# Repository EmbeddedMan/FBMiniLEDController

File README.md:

# FBMiniLEDController
DotStar/NeoPixel controller board for Fubarino Mini chipKIT board

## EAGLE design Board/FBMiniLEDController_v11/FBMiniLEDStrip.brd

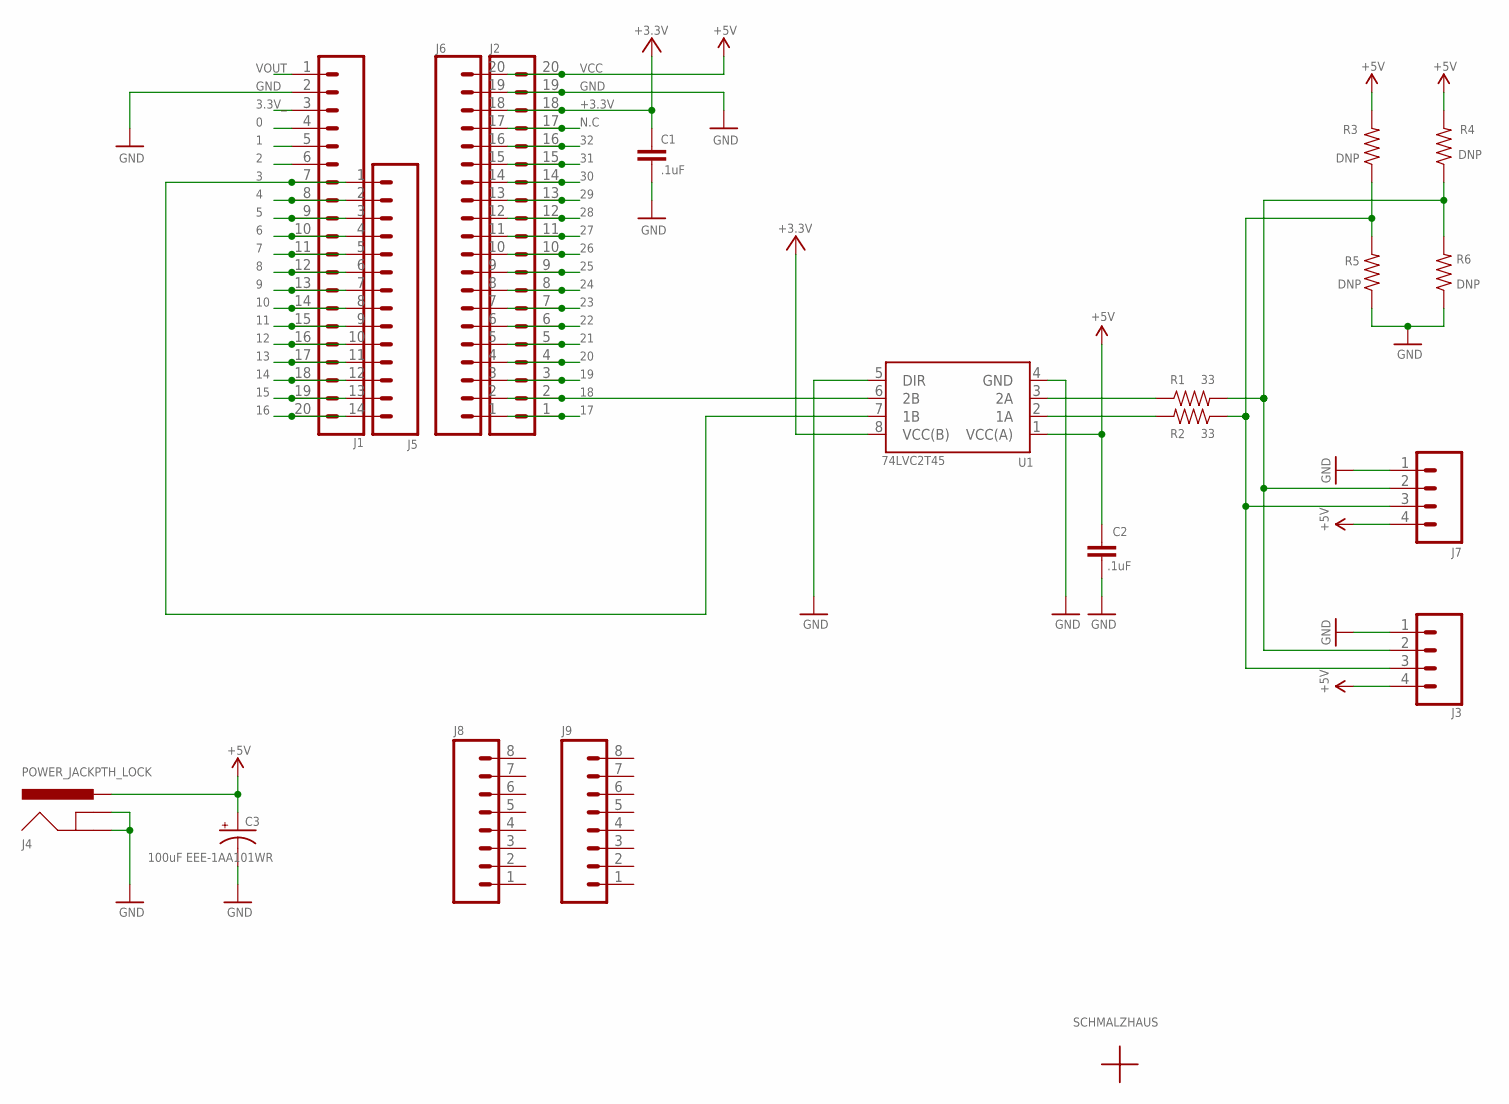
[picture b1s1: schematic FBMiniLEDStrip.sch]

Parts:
C1, C2: .1uF; 0603-CAP
C3: 100uF EEE-1AA101WR; PANASONIC_C
J1, J2, J6: CONN_20; 1X20
J3: CONN_04SCREW; SCREWTERMINAL-3.5MM-4@1
J4: POWER_JACKPTH_LOCK; POWER_JACK_PTH_LOCK
J5: M14; 1X14
J7: M04PTH; 1X04
J8, J9: M08; 1X08_ROUND
R1, R2: 33; 0603-RES
R3, R4, R5, R6: DNP; 0603-RES
U1: 74LVC2T45; VSSOP8
U$1: SCHMALZHAUSSCHMALZHAUS_SMALL; SCHMALZHAUS_SMALL

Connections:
0: J1.4
1: J1.5
2: J1.6
3: J1.7, J5.1, U1.7 (1B)
3.3V_: J1.3
4: J1.8, J5.2
5: J1.9, J5.3
6: J1.10, J5.4
7: J1.11, J5.5
8: J1.12, J5.6
9: J1.13, J5.7
10: J1.14, J5.8
11: J1.15, J5.9
12: J1.16, J5.10
13: J1.17, J5.11
14: J1.18, J5.12
15: J1.19, J5.13
16: J1.20, J5.14
17: J2.1, J6.1
18: J2.2, J6.2, U1.6 (2B)
19: J2.3, J6.3
20: J2.4, J6.4
21: J2.5, J6.5
22: J2.6, J6.6
23: J2.7, J6.7
24: J2.8, J6.8
25: J2.9, J6.9
26: J2.10, J6.10
27: J2.11, J6.11
28: J2.12, J6.12
29: J2.13, J6.13
30: J2.14, J6.14
31: J2.15, J6.15
32: J2.16, J6.16
+3.3V: C1.1, J2.18, J6.18
+3V3: U1.8 (VCC(B))
GND: C1.2, C2.1, C3.-, J1.2, J2.19, J3.1, J4.GND, J4.GNDBREAK, J6.19, J7.1, R5.1, R6.1, U1.4 (GND), U1.5 (DIR)
unnamed: J3.2, J7.2, R1.2, R4.1, R6.2
unnamed: R2.2, U1.2 (1A)
unnamed: J3.3, J7.3, R2.1, R3.1, R5.2
unnamed: R1.1, U1.3 (2A)
N.C: J2.17, J6.17
VCC: C2.2, C3.+, J2.20, J3.4, J4.PWR, J6.20, J7.4, R3.2, R4.2, U1.1 (VCC(A))
VOUT: J1.1

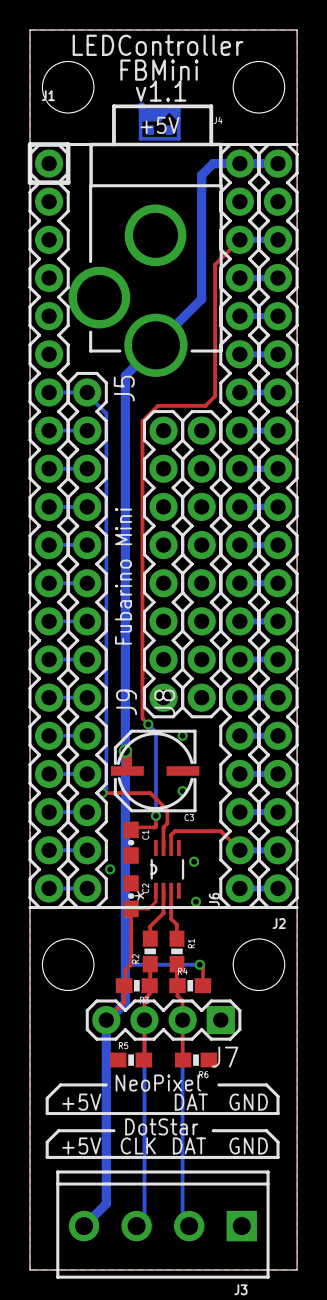
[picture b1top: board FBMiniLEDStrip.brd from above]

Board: 2 copper layers, 17.8 x 82.5 mm, 20 parts (1 on the bottom side), 38 nets.

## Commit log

2017-06-17 Adding initial files.
2017-07-06 Version 1.1 of board - checked out, works great.
2017-07-23 Updated v1.1 schematic with a lot more good information - no board changes.

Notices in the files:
parts and their libraries:
SparkFun-Connectors: Licensing: Creative Commons ShareAlike 4.0 International - https://creativecommons.org/licenses/by-sa/4.0
